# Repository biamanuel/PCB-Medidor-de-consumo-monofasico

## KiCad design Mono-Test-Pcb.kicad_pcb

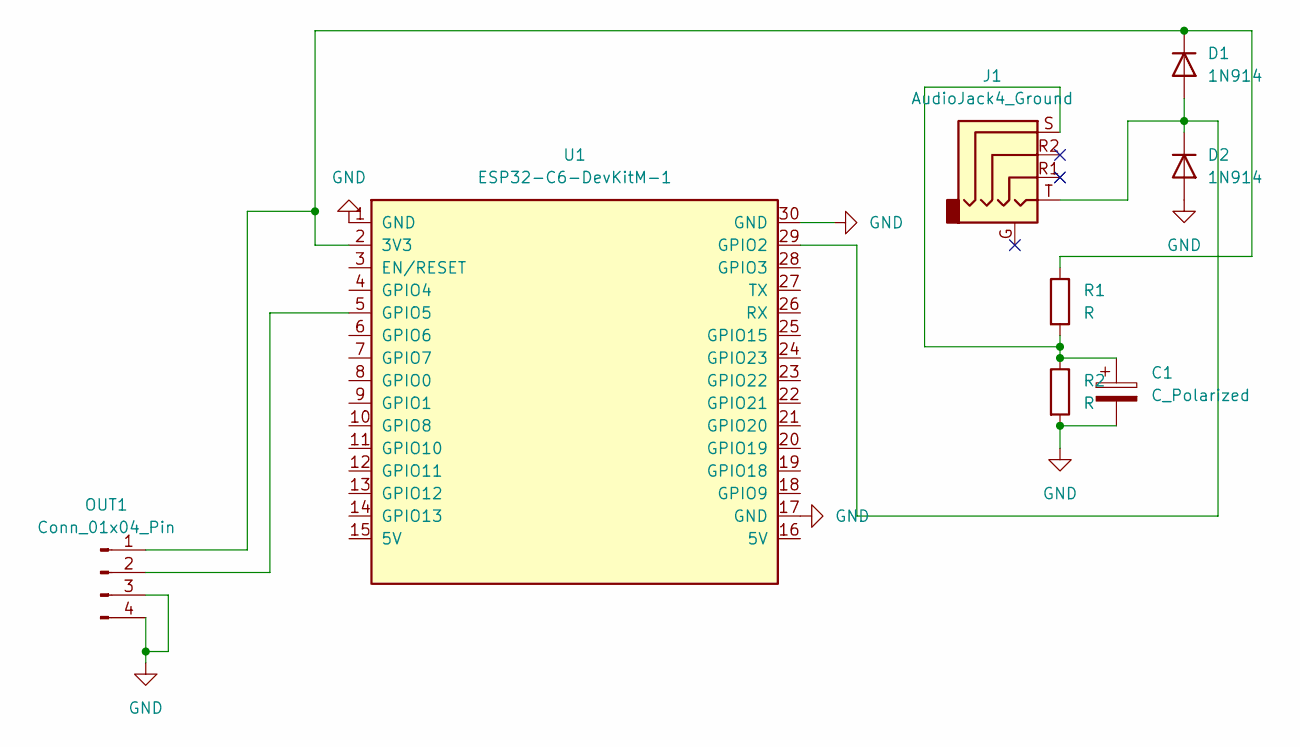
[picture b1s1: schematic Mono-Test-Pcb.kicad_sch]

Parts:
C1: C_Polarized; CP_Radial_D5.0mm_P2.50mm
D1, D2: 1N914; D_DO-35_SOD27_P12.70mm_Horizontal
J1: AudioJack4_Ground; Jack_3.5mm_CUI_SJ1-3515N_Horizontal
OUT1: Conn_01x04_Pin; FanPinHeader_1x04_P2.54mm_Vertical
R1, R2: R; R_Axial_DIN0207_L6.3mm_D2.5mm_P15.24mm_Horizontal
U1: ESP32-C6-DevKitM-1

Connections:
GND: C1.2, D2.2 (A), OUT1.3, OUT1.4, R2.2, U1.1 (GND), U1.17 (GND), U1.30 (GND)
unnamed: C1.1, J1.S, R1.2, R2.1
unnamed: D1.2 (A), D2.1 (K), J1.T, U1.29 (GPIO2)
unnamed: D1.1 (K), OUT1.1, R1.1, U1.2 (3V3)
unnamed: OUT1.2, U1.5 (GPIO5)

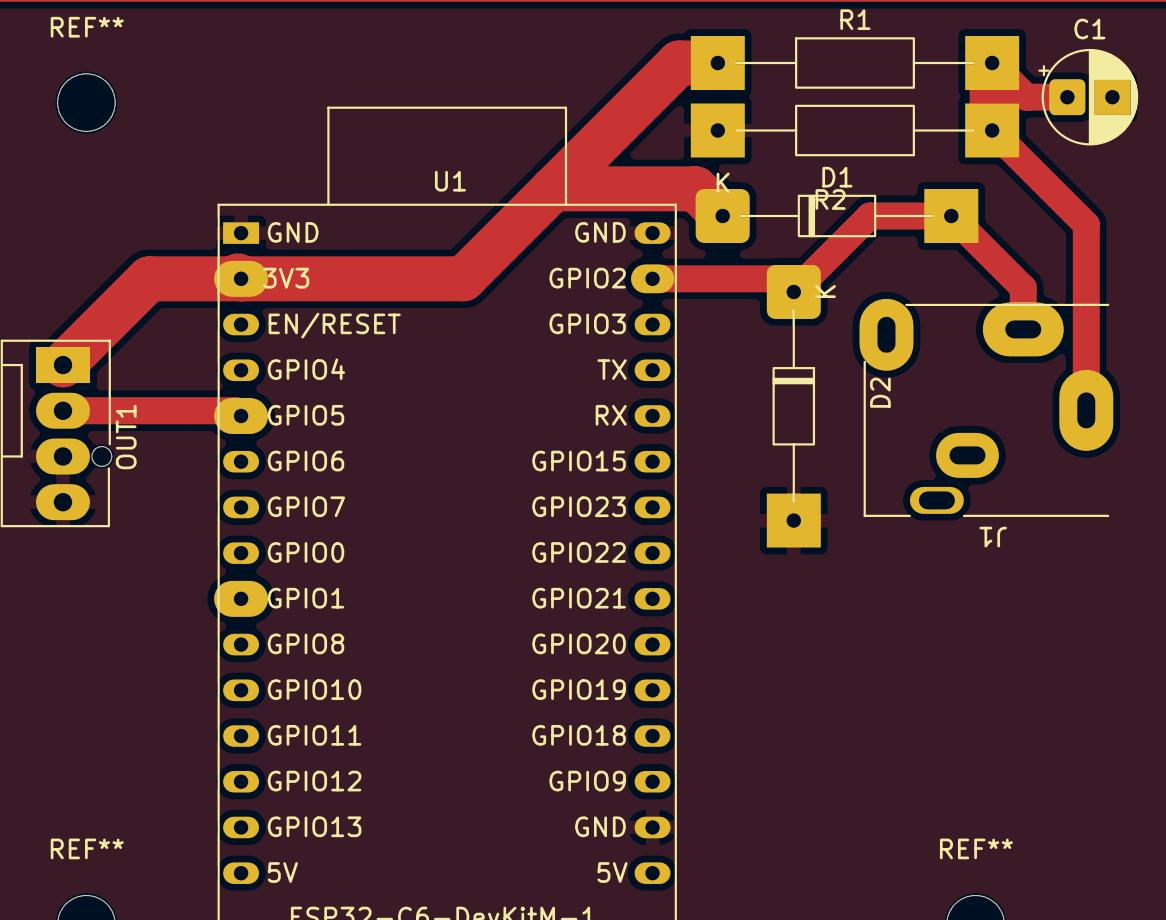
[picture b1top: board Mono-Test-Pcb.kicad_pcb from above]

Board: 2 copper layers, 8 parts (0 on the bottom side), 5 nets.
